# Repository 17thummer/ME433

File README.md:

# ME433
Repository for coursework from Northwestern University's ME433: Advanced Mechatronics class

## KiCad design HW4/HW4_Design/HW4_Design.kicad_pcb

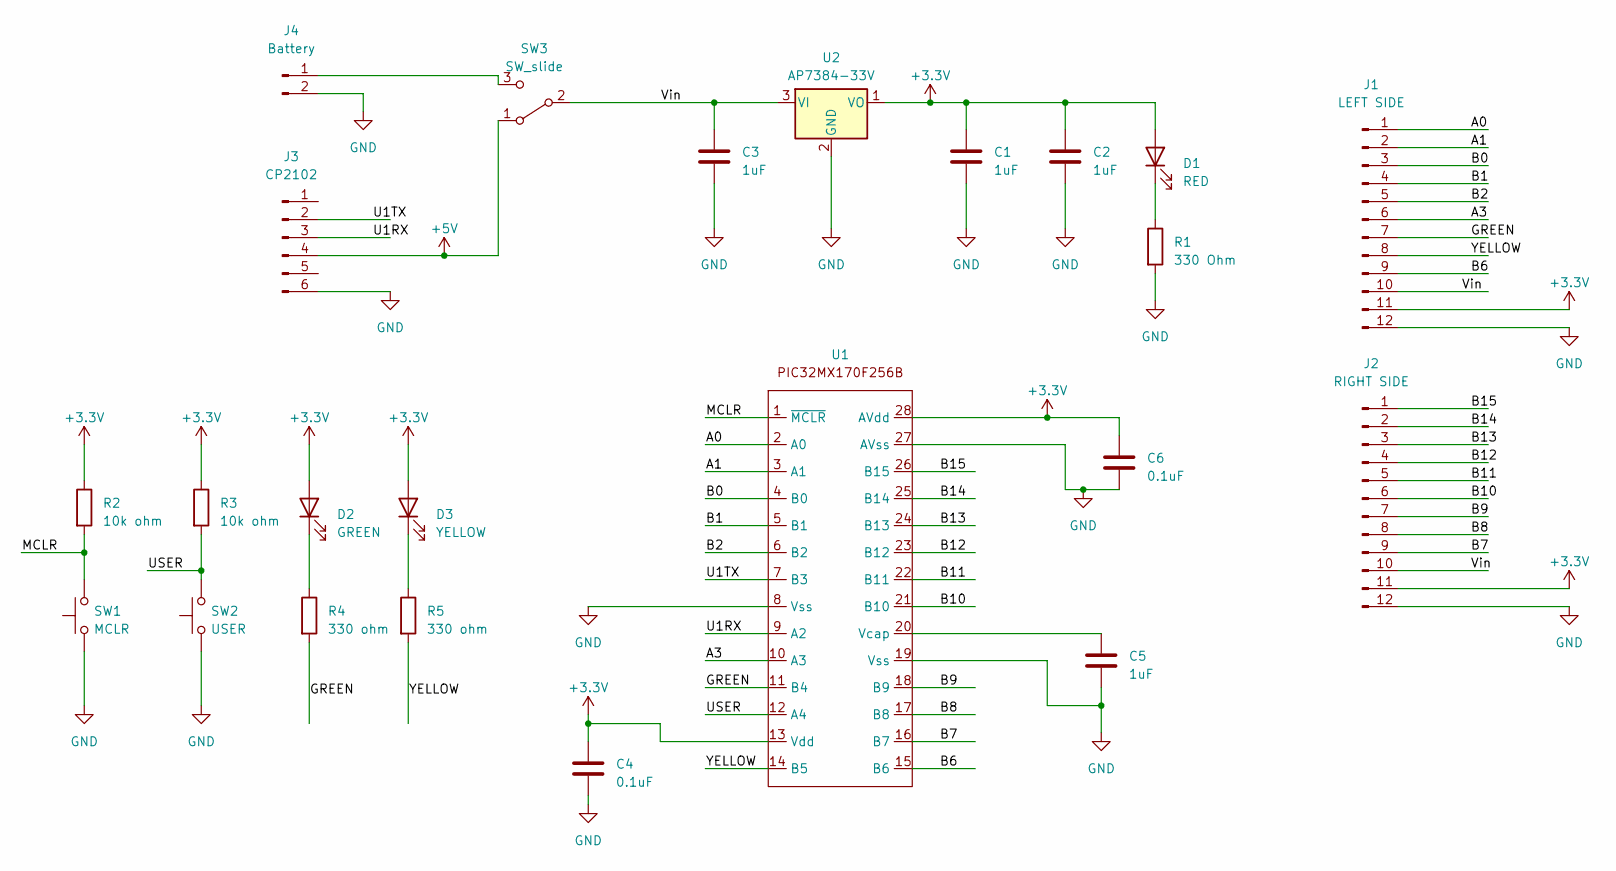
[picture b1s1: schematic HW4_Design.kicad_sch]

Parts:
C1, C2, C3, C5: 1uF; C_Disc_D4.3mm_W1.9mm_P5.00mm
C4, C6: 0.1uF; C_Disc_D3.0mm_W2.0mm_P2.50mm
D1: RED; LED_D3.0mm
D2: GREEN; LED_D3.0mm
D3: YELLOW; LED_D3.0mm
J1: LEFT SIDE; PinSocket_1x12_P2.54mm_Vertical
J2: RIGHT SIDE; PinSocket_1x12_P2.54mm_Vertical
J3: CP2102; PinSocket_1x06_P2.54mm_Vertical
J4: Battery; PinSocket_1x02_P2.54mm_Vertical
R1: 330 Ohm; R_Axial_DIN0207_L6.3mm_D2.5mm_P7.62mm_Horizontal
R2, R3: 10k ohm; R_Axial_DIN0207_L6.3mm_D2.5mm_P7.62mm_Horizontal
R4, R5: 330 ohm; R_Axial_DIN0207_L6.3mm_D2.5mm_P7.62mm_Horizontal
SW1: MCLR; Buttons
SW2: USER; Buttons
SW3: SW_slide; SlideSwitch
U1: DIP-28_W7.62mm_Socket
U2: AP7384-33V; TO-92_Inline_Wide

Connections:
+3.3V: C1.1, C2.1, C4.1, C6.1, D1.2 (A), D2.2 (A), D3.2 (A), J1.11, J2.11, R2.1, R3.1, U1.13 (Vdd), U1.28 (AVdd), U2.1 (VO)
+5V: J3.4, SW3.1 (A)
/A0: J1.1, U1.2 (A0)
/A1: J1.2, U1.3 (A1)
/A3: J1.6, U1.10 (A3)
/B0: J1.3, U1.4 (B0)
/B1: J1.4, U1.5 (B1)
/B2: J1.5, U1.6 (B2)
/B6: J1.9, U1.15 (B6)
/B7: J2.9, U1.16 (B7)
/B8: J2.8, U1.17 (B8)
/B9: J2.7, U1.18 (B9)
/B10: J2.6, U1.21 (B10)
/B11: J2.5, U1.22 (B11)
/B12: J2.4, U1.23 (B12)
/B13: J2.3, U1.24 (B13)
/B14: J2.2, U1.25 (B14)
/B15: J2.1, U1.26 (B15)
/GREEN: J1.7, R4.2, U1.11 (B4)
/MCLR: R2.2, SW1.2, U1.1 (~MCLR)
/U1RX: J3.3, U1.9 (A2)
/U1TX: J3.2, U1.7 (B3)
/USER: R3.2, SW2.2, U1.12 (A4)
/Vin: C3.1, J1.10, J2.10, SW3.2 (B), U2.3 (VI)
/YELLOW: J1.8, R5.2, U1.14 (B5)
GND: C1.2, C2.2, C3.2, C4.2, C5.2, C6.2, J1.12, J2.12, J3.6, J4.2, R1.2, SW1.1, SW2.1, U1.8 (Vss), U1.19 (Vss), U1.27 (AVss), U2.2 (GND)
unnamed: D1.1 (K), R1.1
unnamed: D2.1 (K), R4.1
unnamed: D3.1 (K), R5.1
unnamed: J4.1, SW3.3 (C)
unnamed: C5.1, U1.20 (Vcap)

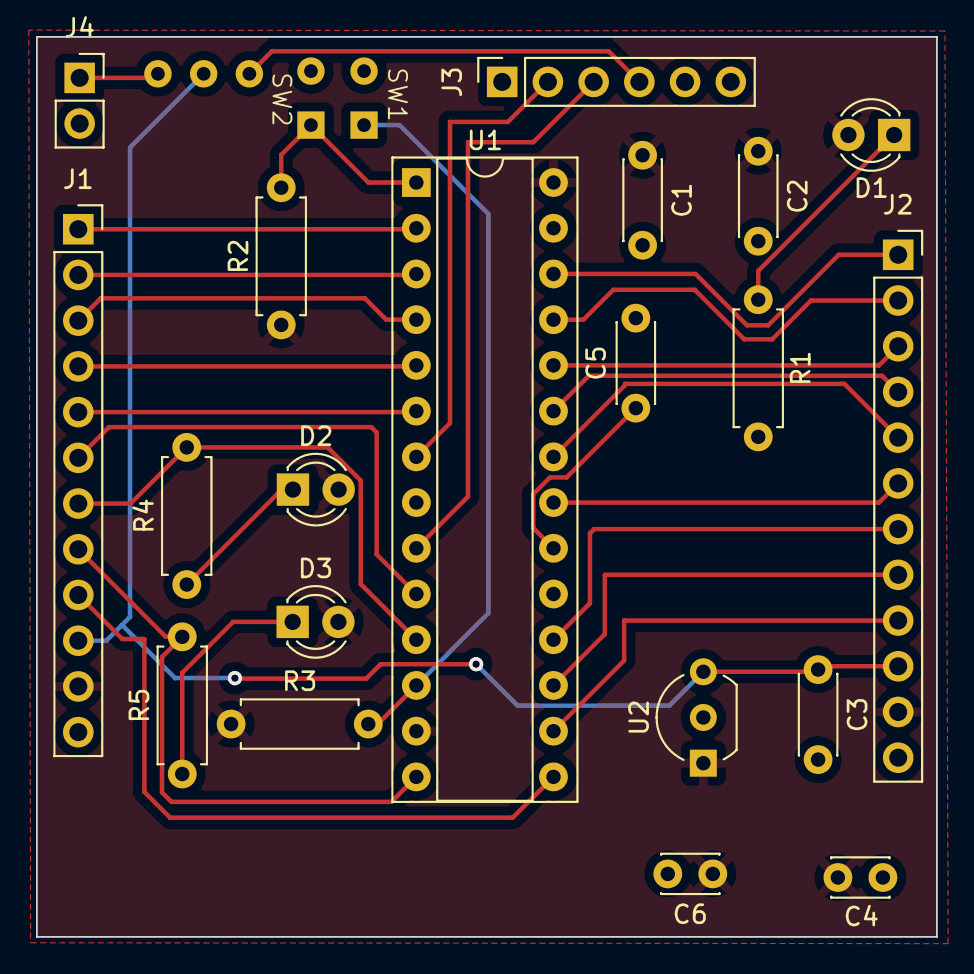
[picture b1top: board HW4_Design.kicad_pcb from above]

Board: 2 copper layers, 50.0 x 50.0 mm, 23 parts (0 on the bottom side), 31 nets.

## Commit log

2023-04-04 add diagrams and circuit image
2023-04-04 edit template
2023-04-05 get mplab running
2023-04-07 Board Layout finish
2023-04-16 Finish HW3
2023-04-18 finish hw5
2023-04-20 create hw6
2023-04-25 finish hw 6
2023-05-03 finish hw 7
2023-05-03 finish hw 8
2023-05-03 halfway through hw 9
2023-05-04 Finish hw 9
2023-05-04 finish hw10
2023-05-23 go back and do hw 4
2023-05-26 finish hw 13
2023-06-07 finish hw 14, 15, and building final project
2023-06-08 finish final project
